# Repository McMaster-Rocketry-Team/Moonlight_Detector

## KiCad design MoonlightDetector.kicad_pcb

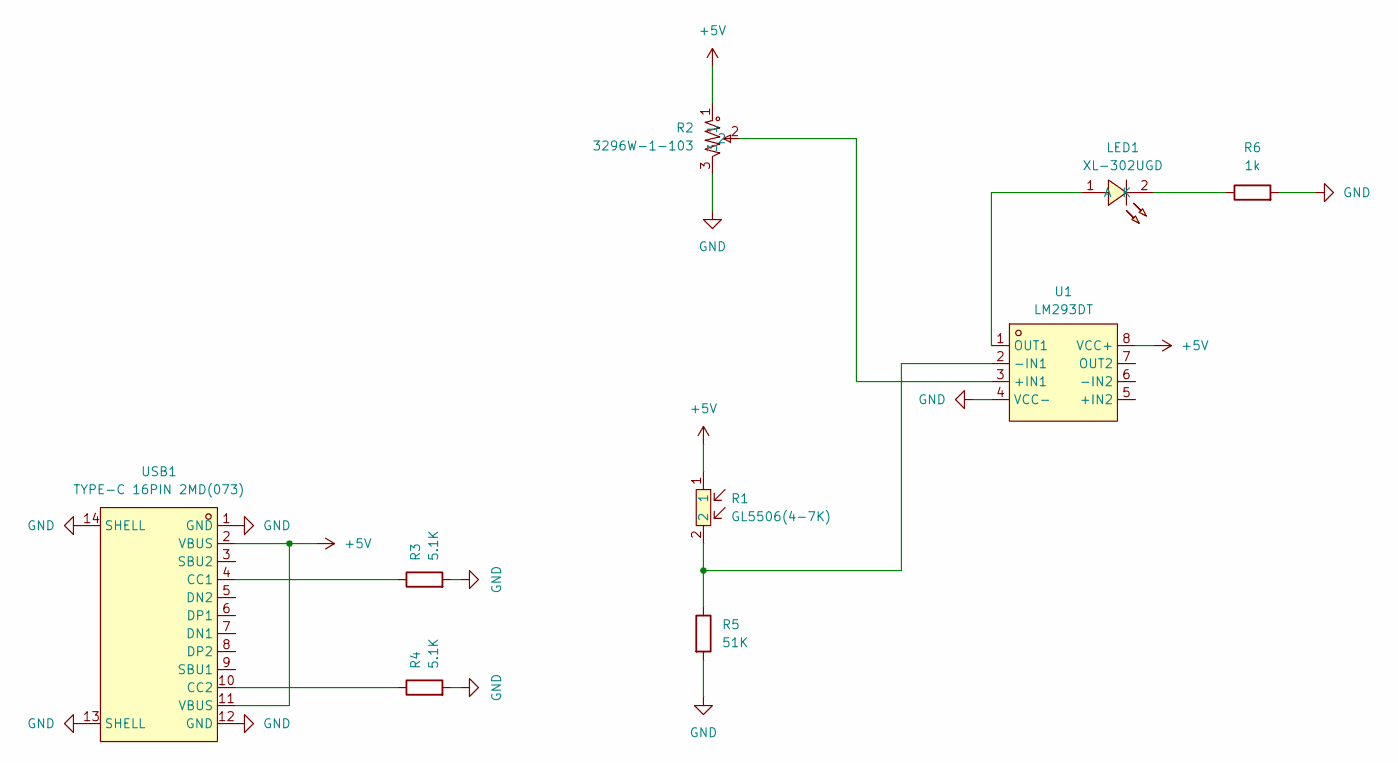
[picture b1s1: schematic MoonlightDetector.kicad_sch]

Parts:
LED1: XL-302UGD; LED-TH_BD3.8-P2.54-FD_GREEN; LCSC Part C2895476
R1: GL5506(4-7K); RES-TH_L5.1-W4.3-P3.00-D0.5; LCSC Part C11299
R2: 3296W-1-103; RES-ADJ-TH_3P-L10.0-W10.0-P2.50-L; LCSC Part C118954
R3, R4: 5.1K; R_0805_2012Metric_Pad1.20x1.40mm_HandSolder
R5: 51K; R_0805_2012Metric_Pad1.20x1.40mm_HandSolder
R6: 1k; R_0805_2012Metric_Pad1.20x1.40mm_HandSolder
U1: LM293DT; SO-8_L4.9-W3.9-P1.27-LS5.9-BL; LCSC Part C76509
USB1: TYPE-C 16PIN 2MD(073); USB-C-SMD_TYPE-C-6PIN-2MD-073; LCSC Part C2765186

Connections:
+5V: R1.1, R2.1, U1.8 (VCC+), USB1.2 (VBUS), USB1.11 (VBUS)
GND: R2.3, R3.2, R4.2, R5.2, R6.2, U1.4 (VCC-), USB1.1 (GND), USB1.12 (GND), USB1.13 (SHELL), USB1.14 (SHELL)
unnamed: LED1.1 (A), U1.1 (OUT1)
unnamed: LED1.2 (K), R6.1
unnamed: R2.2, U1.3 (+IN1)
unnamed: R1.2, R5.1, U1.2 (-IN1)
unnamed: R3.1, USB1.4 (CC1)
unnamed: R4.1, USB1.10 (CC2)

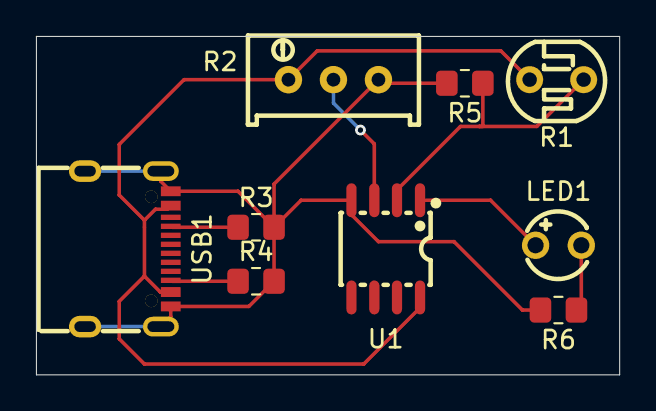
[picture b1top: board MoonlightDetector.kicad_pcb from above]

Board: 2 copper layers, 32.4 x 18.8 mm, 9 parts (0 on the bottom side), 8 nets.

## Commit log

2024-07-20 init commit
2024-07-20 remove backup files
2024-10-06 update simulink model
